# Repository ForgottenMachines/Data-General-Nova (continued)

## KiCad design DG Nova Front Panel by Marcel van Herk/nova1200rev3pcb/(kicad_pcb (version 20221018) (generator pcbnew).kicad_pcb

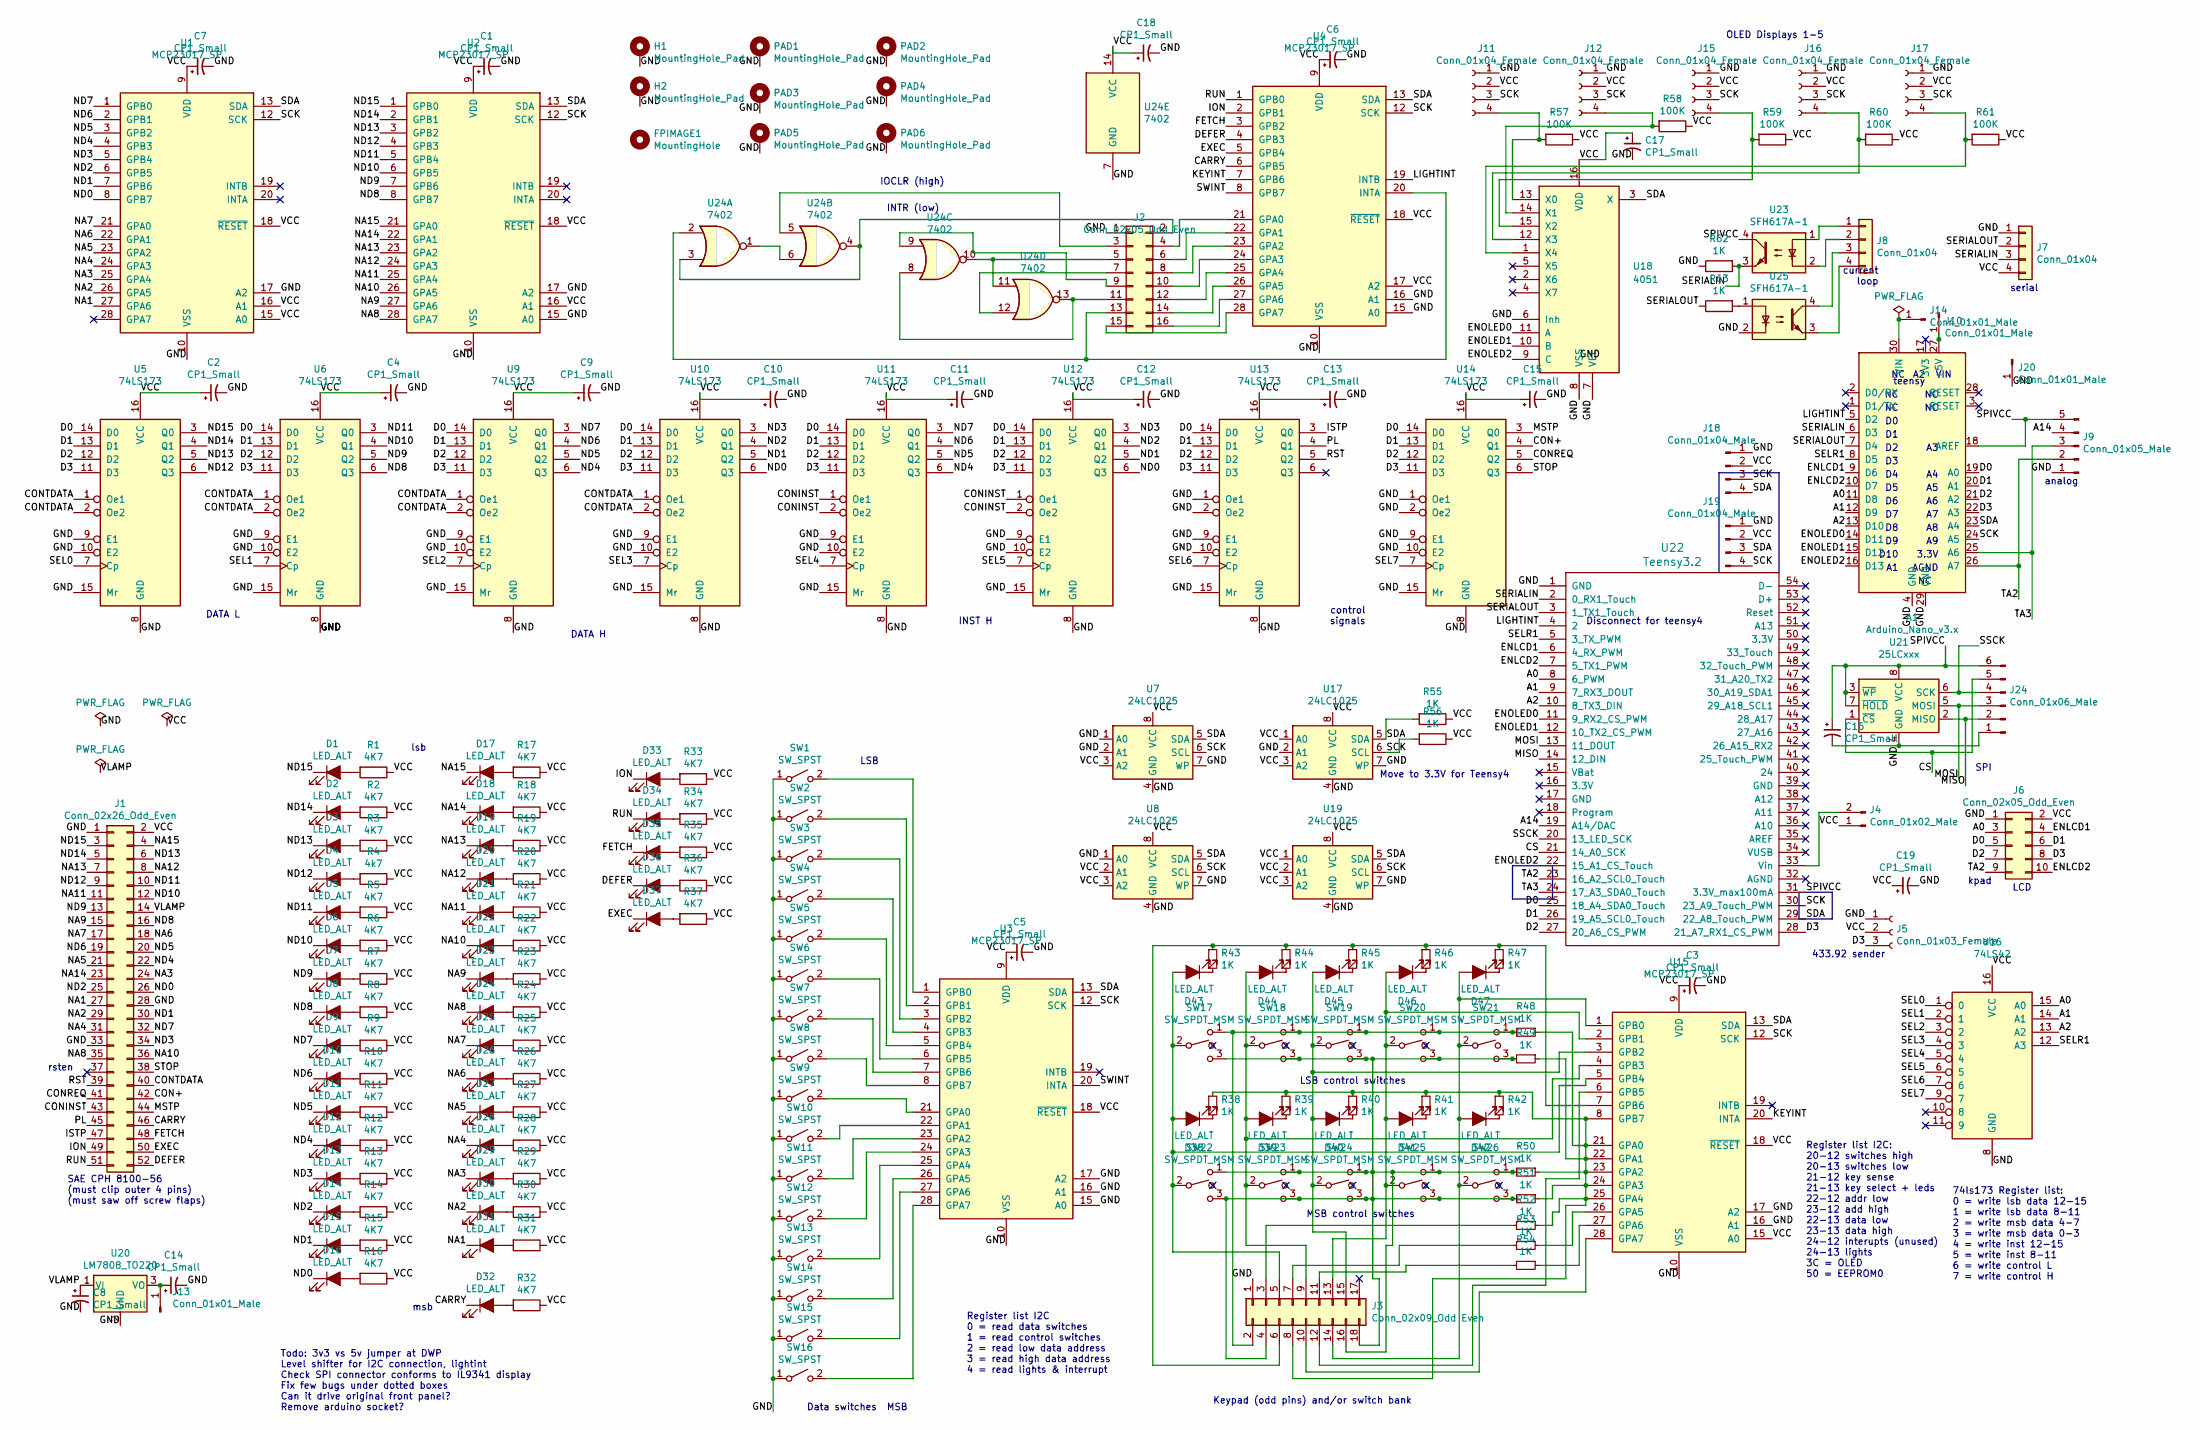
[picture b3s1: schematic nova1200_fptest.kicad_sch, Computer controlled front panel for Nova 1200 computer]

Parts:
A1: Arduino_Nano_v3.x; Arduino_Nano
C1, C2, C3, C4, C5, C6, C7, C8, C9, C10, C11, C12, C13, C14, C15, C16, C17, C18, C19: CP1_Small; CP_Radial_Tantal_D5.0mm_P5.00mm
D1, D2, D3, D4, D5, D6, D7, D8, D9, D10, D11, D12, D13, D14, D15, D16, D17, D18, D19, D20, D21, D22, D23, D24, D25, D26, D27, D28, D29, D30, D31, D32, D33, D34, D35, D36, D37, D38, D39, D40, D41, D42, D43, D44, D45, D46, D47: LED_ALT; LED_D5.0mm_Clear
FPIMAGE1: MountingHole; nova frontpanel layout
H1, H2: MountingHole_Pad; MountingHole_2.2mm_M2_Pad
J1: Conn_02x26_Odd_Even; nova_fp
J2: Conn_02x05_Odd_Even; PinHeader_2x08_P2.54mm_Vertical
J3: Conn_02x09_Odd Even; PinHeader_2x09_P2.54mm_Vertical
J4: Conn_01x02_Male; PinHeader_1x02_P2.54mm_Vertical
J5: Conn_01x03_Female; PinSocket_1x03_P2.54mm_Vertical
J6: Conn_02x05_Odd_Even; PinHeader_2x05_P2.54mm_Vertical
J7, J8: Conn_01x04; PinHeader_1x04_P2.54mm_Vertical
J9: Conn_01x05_Male; PinHeader_1x05_P2.54mm_Vertical
J10, J13, J14, J20: Conn_01x01_Male; PinHeader_1x01_P2.54mm_Vertical
J11, J12, J15, J16, J17: Conn_01x04_Female; PinSocket_1x04_P2.54mm_Vertical
J18, J19: Conn_01x04_Male; PinSocket_1x04_P2.54mm_Vertical
J24: Conn_01x06_Male; PinHeader_1x06_P2.54mm_Vertical
PAD1, PAD2, PAD3, PAD4, PAD5, PAD6: MountingHole_Pad; MountingHole_3.2mm_M3_Pad
R1, R2, R3, R5, R6, R7, R8, R9, R10, R11, R12, R13, R14, R15, R16, R17, R18, R19, R20, R21, R22, R23, R24, R25, R26, R27, R28, R29, R30, R31, R32, R33, R34, R35, R36, R37: 4K7; R_Axial_DIN0204_L3.6mm_D1.6mm_P7.62mm_Horizontal
R4: 4k7; R_Axial_DIN0204_L3.6mm_D1.6mm_P7.62mm_Horizontal
R38, R39, R40, R41, R42, R43, R44, R45, R46, R47, R48, R49, R50, R51, R52, R53, R54, R55, R56, R62, R63: 1K; R_Axial_DIN0204_L3.6mm_D1.6mm_P7.62mm_Horizontal
R57, R58, R59, R60, R61: 100K; R_Axial_DIN0204_L3.6mm_D1.6mm_P7.62mm_Horizontal
SW1, SW2, SW3, SW4, SW5, SW6, SW7, SW8, SW9, SW10, SW11, SW12, SW13, SW14, SW15, SW16: SW_SPST; multicomp switch
SW17, SW18, SW19, SW20, SW21, SW22, SW23, SW24, SW25, SW26: SW_SPDT_MSM; multicomp switch
U1, U2, U3, U4, U15: MCP23017_SP; DIP-28_W7.62mm
U5, U6, U9, U10, U11, U12, U13, U14: 74LS173; DIP-16_W7.62mm
U7, U8, U17, U19: 24LC1025; DIP-8_W7.62mm
U16: 74LS42; DIP-16_W7.62mm
U18: 4051; DIP-16_W7.62mm
U20: LM7808_TO220; TO-220-3_Horizontal_TabDown
U21: 25LCxxx; DIP-8_W7.62mm
U22: Teensy3.2; Teensy30_31_32_LC
U23, U25: SFH617A-1; DIP-4_W7.62mm
U24: 7402; DIP-14_W7.62mm

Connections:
/A0: A1.11 (D8), J6.3, U16.15 (A0), U22.8 (6_PWM)
/A1: A1.12 (D9), U16.14 (A1), U22.9 (7_RX3_DOUT)
/A2: A1.13 (D10), U16.13 (A2), U22.10 (8_TX3_DIN)
/A14: J9.4, U22.19 (A14/DAC)
/CARRY: D32.1 (K), J1.46, U4.6 (GPB5)
/CON+: J1.42, U14.4 (Q1)
/CONINST: J1.43, U11.1 (Oe1), U11.2 (Oe2), U12.1 (Oe1), U12.2 (Oe2)
/CONREQ: J1.41, U14.5 (Q2)
/CONTDATA: J1.40, U5.1 (Oe1), U5.2 (Oe2), U6.1 (Oe1), U6.2 (Oe2), U9.1 (Oe1), U9.2 (Oe2), U10.1 (Oe1), U10.2 (Oe2)
/CS: J24.5, U21.1 (~CS), U22.21 (14_A0_SCK)
/D0: A1.19 (A0), J6.5, U5.14 (D0), U6.14 (D0), U9.14 (D0), U10.14 (D0), U11.14 (D0), U12.14 (D0), U13.14 (D0), U14.14 (D0), U22.25 (18_A4_SDA0_Touch)
/D1: A1.20 (A1), J6.6, U5.13 (D1), U6.13 (D1), U9.13 (D1), U10.13 (D1), U11.13 (D1), U12.13 (D1), U13.13 (D1), U14.13 (D1), U22.26 (19_A5_SCL0_Touch)
/D2: A1.21 (A2), J6.7, U5.12 (D2), U6.12 (D2), U9.12 (D2), U10.12 (D2), U11.12 (D2), U12.12 (D2), U13.12 (D2), U14.12 (D2), U22.27 (20_A6_CS_PWM)
/D3: A1.22 (A3), J5.3, J6.8, U5.11 (D3), U6.11 (D3), U9.11 (D3), U10.11 (D3), U11.11 (D3), U12.11 (D3), U13.11 (D3), U14.11 (D3), U22.28 (21_A7_RX1_CS_PWM)
/DEFER: D36.1 (K), J1.52, U4.4 (GPB3)
/ENLCD1: A1.9 (D6), J6.4, U22.6 (4_RX_PWM)
/ENLCD2: A1.10 (D7), J6.10, U22.7 (5_TX1_PWM)
/ENOLED0: A1.14 (D11), U18.11 (A), U22.11 (9_RX2_CS_PWM)
/ENOLED1: A1.15 (D12), U18.10 (B), U22.12 (10_TX2_CS_PWM)
/ENOLED2: A1.16 (D13), U18.9 (C), U22.22 (15_A1_CS_Touch)
/EXEC: D37.1 (K), J1.50, U4.5 (GPB4)
/FETCH: D35.1 (K), J1.48, U4.3 (GPB2)
/GND: A1.4 (GND), A1.29 (GND), C1.2, C2.2, C3.2, C4.2, C5.2, C6.2, C7.2, C8.2, C9.2, C10.2, C11.2, C12.2, C13.2, C14.2, C15.2, C16.2, C17.2, C18.2, C19.2, H1.1, H2.1, J1.1, J1.28, J1.33, J2.1, J3.1, J5.1, J6.1, J7.1, J9.1, J11.1, J12.1, J15.1, J16.1, J17.1, J18.1, J19.1, J20.1, J24.1, PAD1.1, PAD2.1, PAD3.1, PAD4.1, PAD5.1, PAD6.1, R62.1, SW1.1 (A), SW2.1 (A), SW3.1 (A), SW4.1 (A), SW5.1 (A), SW6.1 (A), SW7.1 (A), SW8.1 (A), SW9.1 (A), SW10.1 (A), SW11.1 (A), SW12.1 (A), SW13.1 (A), SW14.1 (A), SW15.1 (A), SW16.1 (A), U1.10 (VSS), U1.17 (A2), U2.10 (VSS), U2.15 (A0), U2.17 (A2), U3.10 (VSS), U3.15 (A0), U3.16 (A1), U3.17 (A2), U4.10 (VSS), U4.15 (A0), U4.16 (A1), U5.8 (GND), U5.9 (E1), U5.10 (E2), U5.15 (Mr), U6.8 (GND), U6.9 (E1), U6.10 (E2), U6.15 (Mr), U7.1 (A0), U7.2 (A1), U7.4 (GND), U7.7 (WP), U8.1 (A0), U8.4 (GND), U8.7 (WP), U9.8 (GND), U9.9 (E1), U9.10 (E2), U9.15 (Mr), U10.8 (GND), U10.9 (E1), U10.10 (E2), U10.15 (Mr), U11.8 (GND), U11.9 (E1), U11.10 (E2), U11.15 (Mr), U12.8 (GND), U12.9 (E1), U12.10 (E2), U12.15 (Mr), U13.1 (Oe1), U13.2 (Oe2), U13.8 (GND), U13.9 (E1), U13.10 (E2), U13.15 (Mr), U14.1 (Oe1), U14.2 (Oe2), U14.8 (GND), U14.9 (E1), U14.10 (E2), U14.15 (Mr), U15.10 (VSS), U15.16 (A1), U15.17 (A2), U16.8 (GND), U17.2 (A1), U17.4 (GND), U17.7 (WP), U18.6 (Inh), U18.7 (VEE), U18.8 (VSS), U19.4 (GND), U19.7 (WP), U20.2 (GND), U21.4 (GND), U22.1 (GND), U24.7 (GND), U25.2
/ION: D33.1 (K), J1.49, U4.2 (GPB1)
/ISTP: J1.47, U13.3 (Q0)
/KEYINT: U4.7 (GPB6), U15.20 (INTA)
/LIGHTINT: A1.5 (D2), U4.19 (INTB), U22.4 (2)
/MISO: J24.2, U21.2 (MISO), U22.14 (12_DIN)
/MOSI: J24.3, U21.5 (MOSI), U22.13 (11_DOUT)
/MSTP: J1.44, U14.3 (Q0)
/NA1: D31.1 (K), J1.27, U1.27 (GPA6)
/NA2: D30.1 (K), J1.29, U1.26 (GPA5)
/NA3: D29.1 (K), J1.24, U1.25 (GPA4)
/NA4: D28.1 (K), J1.31, U1.24 (GPA3)
/NA5: D27.1 (K), J1.21, U1.23 (GPA2)
/NA6: D26.1 (K), J1.18, U1.22 (GPA1)
/NA7: D25.1 (K), J1.17, U1.21 (GPA0)
/NA8: D24.1 (K), J1.35, U2.28 (GPA7)
/NA9: D23.1 (K), J1.15, U2.27 (GPA6)
/NA10: D22.1 (K), J1.36, U2.26 (GPA5)
/NA11: D21.1 (K), J1.11, U2.25 (GPA4)
/NA12: D20.1 (K), J1.8, U2.24 (GPA3)
/NA13: D19.1 (K), J1.7, U2.23 (GPA2)
/NA14: D18.1 (K), J1.23, U2.22 (GPA1)
/NA15: D17.1 (K), J1.4, U2.21 (GPA0)
/ND0: D16.1 (K), J1.26, U1.8 (GPB7), U10.6 (Q3), U12.6 (Q3)
/ND1: D15.1 (K), J1.30, U1.7 (GPB6), U10.5 (Q2), U12.5 (Q2)
/ND2: D14.1 (K), J1.25, U1.6 (GPB5), U10.4 (Q1), U12.4 (Q1)
/ND3: D13.1 (K), J1.34, U1.5 (GPB4), U10.3 (Q0), U12.3 (Q0)
/ND4: D12.1 (K), J1.22, U1.4 (GPB3), U9.6 (Q3), U11.6 (Q3)
/ND5: D11.1 (K), J1.20, U1.3 (GPB2), U9.5 (Q2), U11.5 (Q2)
/ND6: D10.1 (K), J1.19, U1.2 (GPB1), U9.4 (Q1), U11.4 (Q1)
/ND7: D9.1 (K), J1.32, U1.1 (GPB0), U9.3 (Q0), U11.3 (Q0)
/ND8: D8.1 (K), J1.16, U2.8 (GPB7), U6.6 (Q3)
/ND9: D7.1 (K), J1.13, U2.7 (GPB6), U6.5 (Q2)
/ND10: D6.1 (K), J1.12, U2.6 (GPB5), U6.4 (Q1)
/ND11: D5.1 (K), J1.10, U2.5 (GPB4), U6.3 (Q0)
/ND12: D4.1 (K), J1.9, U2.4 (GPB3), U5.6 (Q3)
/ND13: D3.1 (K), J1.6, U2.3 (GPB2), U5.5 (Q2)
/ND14: D2.1 (K), J1.5, U2.2 (GPB1), U5.4 (Q1)
/ND15: D1.1 (K), J1.3, U2.1 (GPB0), U5.3 (Q0)
/PL: J1.45, U13.4 (Q1)
/RST: J1.39, U13.5 (Q2)
/RUN: D34.1 (K), J1.51, U4.1 (GPB0)
/SCK: A1.24 (A5), J11.3, J12.3, J15.3, J16.3, J17.3, J18.3, J19.4, R56.2, U1.12 (SCK), U2.12 (SCK), U3.12 (SCK), U4.12 (SCK), U7.6 (SCL), U8.6 (SCL), U15.12 (SCK), U17.6 (SCL), U19.6 (SCL), U22.30 (23_A9_Touch_PWM)
/SDA: A1.23 (A4), J18.4, J19.3, R55.2, U1.13 (SDA), U2.13 (SDA), U3.13 (SDA), U4.13 (SDA), U7.5 (SDA), U8.5 (SDA), U15.13 (SDA), U17.5 (SDA), U18.3 (X), U19.5 (SDA), U22.29 (22_A8_Touch_PWM)
/SEL0: U5.7 (Cp), U16.1 (0)
/SEL1: U6.7 (Cp), U16.2 (1)
/SEL2: U9.7 (Cp), U16.3 (2)
/SEL3: U10.7 (Cp), U16.4 (3)
/SEL4: U11.7 (Cp), U16.5 (4)
/SEL5: U12.7 (Cp), U16.6 (5)
/SEL6: U13.7 (Cp), U16.7 (6)
/SEL7: U14.7 (Cp), U16.9 (7)
/SELR1: A1.8 (D5), U16.12 (A3), U22.5 (3_TX_PWM)
/SERIALIN: A1.6 (D3), J7.3, R62.2, U22.2 (0_RX1_Touch), U23.3
/SERIALOUT: A1.7 (D4), J7.2, R63.1, U22.3 (1_TX1_Touch)
/SPIVCC: A1.18 (AREF), C16.1, J9.5, J24.6, U21.3 (~WP), U21.7 (~HOLD), U21.8 (VCC), U22.31 (3.3V_max100mA), U23.4
/SSCK: J24.4, U21.6 (SCK), U22.20 (13_LED_SCK)
/STOP: J1.38, U14.6 (Q3)
/SWINT: U3.20 (INTA), U4.8 (GPB7)
/TA2: A1.26 (A7), J6.9, J9.2, U22.23 (16_A2_SCL0_Touch)
/TA3: A1.25 (A6), J9.3, U22.24 (17_A3_SDA0_Touch)
/VCC: C1.1, C2.1, C3.1, C4.1, C5.1, C6.1, C7.1, C9.1, C10.1, C11.1, C12.1, C13.1, C15.1, C17.1, C18.1, C19.1, J1.2, J4.1, J5.2, J6.2, J7.4, J11.2, J12.2, J15.2, J16.2, J17.2, J18.2, J19.2, R1.1, R2.1, R3.1, R4.1, R5.1, R6.1, R7.1, R8.1, R9.1, R10.1, R11.1, R12.1, R13.1, R14.1, R15.1, R16.1, R17.1, R18.1, R19.1, R20.1, R21.1, R22.1, R23.1, R24.1, R25.1, R26.1, R27.1, R28.1, R29.1, R30.1, R31.1, R32.1, R33.1, R34.1, R35.1, R36.1, R37.1, R55.1, R56.1, R57.1, R58.1, R59.1, R60.1, R61.1, U1.9 (VDD), U1.15 (A0), U1.16 (A1), U1.18 (~RESET), U2.9 (VDD), U2.16 (A1), U2.18 (~RESET), U3.9 (VDD), U3.18 (~RESET), U4.9 (VDD), U4.17 (A2), U4.18 (~RESET), U5.16 (VCC), U6.16 (VCC), U7.3 (A2), U7.8 (VCC), U8.2 (A1), U8.3 (A2), U8.8 (VCC), U9.16 (VCC), U10.16 (VCC), U11.16 (VCC), U12.16 (VCC), U13.16 (VCC), U14.16 (VCC), U15.9 (VDD), U15.15 (A0), U15.18 (~RESET), U16.16 (VCC), U17.1 (A0), U17.3 (A2), U17.8 (VCC), U18.16 (VDD), U19.1 (A0), U19.2 (A1), U19.3 (A2), U19.8 (VCC), U24.14 (VCC)
/VLAMP: C8.1, J1.14, U20.1 (VI)
unnamed: A1.27 (+5V), J10.1
unnamed: A1.30 (VIN), J14.1
unnamed: C14.1, J13.1, U20.3 (VO)
unnamed: D1.2 (A), R1.2
unnamed: D2.2 (A), R2.2
unnamed: D3.2 (A), R3.2
unnamed: D4.2 (A), R4.2
unnamed: D5.2 (A), R5.2
unnamed: D6.2 (A), R6.2
unnamed: D7.2 (A), R7.2
unnamed: D8.2 (A), R8.2
unnamed: D9.2 (A), R9.2
unnamed: D10.2 (A), R10.2
unnamed: D11.2 (A), R11.2
unnamed: D12.2 (A), R12.2
unnamed: D13.2 (A), R13.2
unnamed: D14.2 (A), R14.2
unnamed: D15.2 (A), R15.2
unnamed: D16.2 (A), R16.2
unnamed: D17.2 (A), R17.2
unnamed: D18.2 (A), R18.2
unnamed: D19.2 (A), R19.2
unnamed: D20.2 (A), R20.2
unnamed: D21.2 (A), R21.2
unnamed: D22.2 (A), R22.2
unnamed: D23.2 (A), R23.2
unnamed: D24.2 (A), R24.2
unnamed: D25.2 (A), R25.2
unnamed: D26.2 (A), R26.2
unnamed: D27.2 (A), R27.2
unnamed: D28.2 (A), R28.2
unnamed: D29.2 (A), R29.2
unnamed: D30.2 (A), R30.2
unnamed: D31.2 (A), R31.2
unnamed: D32.2 (A), R32.2
unnamed: D33.2 (A), R33.2
unnamed: D34.2 (A), R34.2
unnamed: D35.2 (A), R35.2
unnamed: D36.2 (A), R36.2
unnamed: D37.2 (A), R37.2
unnamed: D38.1 (K), R38.2
unnamed: D38.2 (A), D43.2 (A), J3.5, SW17.2, SW22.2, U15.5 (GPB4)
unnamed: D39.1 (K), R39.2
unnamed: D39.2 (A), D44.2 (A), J3.9, SW18.2, SW23.2, U15.4 (GPB3)
unnamed: D40.1 (K), R40.2
unnamed: D40.2 (A), D45.2 (A), J3.15, SW19.2, SW24.2, U15.3 (GPB2)
unnamed: D41.1 (K), R41.2
unnamed: D41.2 (A), D46.2 (A), J3.13, SW20.2, SW25.2, U15.2 (GPB1)
unnamed: D42.1 (K), R42.2
unnamed: D42.2 (A), D47.2 (A), J3.14, SW21.2, SW26.2, U15.1 (GPB0)
unnamed: D43.1 (K), R43.2
unnamed: D44.1 (K), R44.2
unnamed: D45.1 (K), R45.2
unnamed: D46.1 (K), R46.2
unnamed: D47.1 (K), R47.2
unnamed: J2.2, U24.3, U24.4
unnamed: J2.3, U24.5
unnamed: J2.4, U4.21 (GPA0)
unnamed: J2.5, U24.10, U24.11
unnamed: J2.6, U4.22 (GPA1)
unnamed: J2.7, U24.12
unnamed: J2.8, U4.23 (GPA2)
unnamed: J2.9, U24.9
unnamed: J2.10, U4.24 (GPA3)
unnamed: J2.11, U24.8, U24.13
unnamed: J2.12, U4.25 (GPA4)
unnamed: J2.13, U4.20 (INTA), U24.2
unnamed: J2.14, U4.26 (GPA5)
unnamed: J2.15, U4.28 (GPA7)
unnamed: J2.16, U4.27 (GPA6)
unnamed: J3.2, R48.2, SW17.1, SW18.1, SW19.1, SW20.1, SW21.1
unnamed: J3.3, R52.2
unnamed: J3.6, R43.1, R44.1, R45.1, R46.1, R47.1, U15.7 (GPB6)
unnamed: J3.7, R53.2
unnamed: J3.10, U15.28 (GPA7)
unnamed: J3.11, R54.2
unnamed: J3.12, U15.6 (GPB5)
unnamed: J4.2, U22.33 (Vin)
unnamed: J8.1, U23.1
unnamed: J8.2, U23.2
unnamed: J8.3, U25.4
unnamed: J8.4, U25.3
unnamed: J11.4, R57.2, U18.13 (X0)
unnamed: J12.4, R58.2, U18.14 (X1)
unnamed: J15.4, R59.2, U18.15 (X2)
unnamed: J16.4, R60.2, U18.12 (X3)
unnamed: J17.4, R61.2, U18.1 (X4)
unnamed: R53.1, U15.26 (GPA5)
unnamed: R54.1, U15.27 (GPA6)
unnamed: R63.2, U25.1
unnamed: SW1.2 (B), U3.1 (GPB0)
unnamed: SW2.2 (B), U3.2 (GPB1)
unnamed: SW3.2 (B), U3.3 (GPB2)
unnamed: SW4.2 (B), U3.4 (GPB3)
unnamed: SW5.2 (B), U3.5 (GPB4)
unnamed: SW6.2 (B), U3.6 (GPB5)
unnamed: SW7.2 (B), U3.7 (GPB6)
unnamed: SW8.2 (B), U3.8 (GPB7)
unnamed: SW9.2 (B), U3.21 (GPA0)
unnamed: SW10.2 (B), U3.22 (GPA1)
unnamed: SW11.2 (B), U3.23 (GPA2)
unnamed: SW12.2 (B), U3.24 (GPA3)
unnamed: SW13.2 (B), U3.25 (GPA4)
unnamed: SW14.2 (B), U3.26 (GPA5)
unnamed: SW15.2 (B), U3.27 (GPA6)
unnamed: SW16.2 (B), U3.28 (GPA7)
unnamed: U24.1, U24.6

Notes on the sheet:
433.92 sender
Keypad (odd pins) and/or switch bank
74ls173 Register list: 0 = write lsb data 12-15 1 = write lsb data 8-11 2 = write msb data 4-7 3 = write msb data 0-3 4 = write inst 12-15 5 = write inst 8-11 6 = write control L 7 = write control H
rsten
SAE CPH 8100-56 (must clip outer 4 pins) (must saw off screw flaps)
D10
teensy
AGND
Data switches
Move to 3.3V for Teensy4
MSB
INST H
LCD
VIN
LSB control switches
control signals
INTR (low)
OLED Displays 1-5
DATA H
lsb
Register list I2C 0 = read data switches 1 = read control switches 2 = read low data address 3 = read high data address 4 = read lights & interrupt
3.3V
Todo: 3v3 vs 5v jumper at DWP Level shifter for I2C connection, lightint Check SPI connector conforms to IL9341 display Fix few bugs under dotted boxes Can it drive original front panel? Remove arduino socket?
analog
DATA L
msb
kpad
SPI
Register list I2C: 20-12 switches high 20-13 switches low 21-12 key sense 21-13 key select + leds 22-12 addr low 23-12 add high 22-13 data low 23-13 data high 24-12 interupts (unused) 24-13 lights 3C = OLED 50 = EEPROM0
serial
Disconnect for teensy4
MSB control switches
LSB
current loop
IOCLR (high)

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
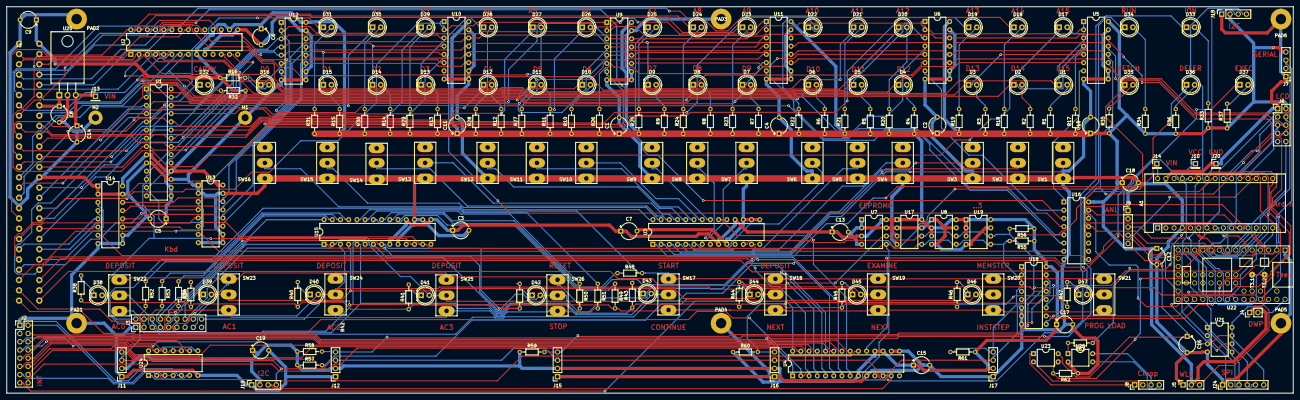
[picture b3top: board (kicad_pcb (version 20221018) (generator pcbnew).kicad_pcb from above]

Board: 2 copper layers, 397.5 x 119.4 mm, 211 parts (0 on the bottom side), 201 nets.

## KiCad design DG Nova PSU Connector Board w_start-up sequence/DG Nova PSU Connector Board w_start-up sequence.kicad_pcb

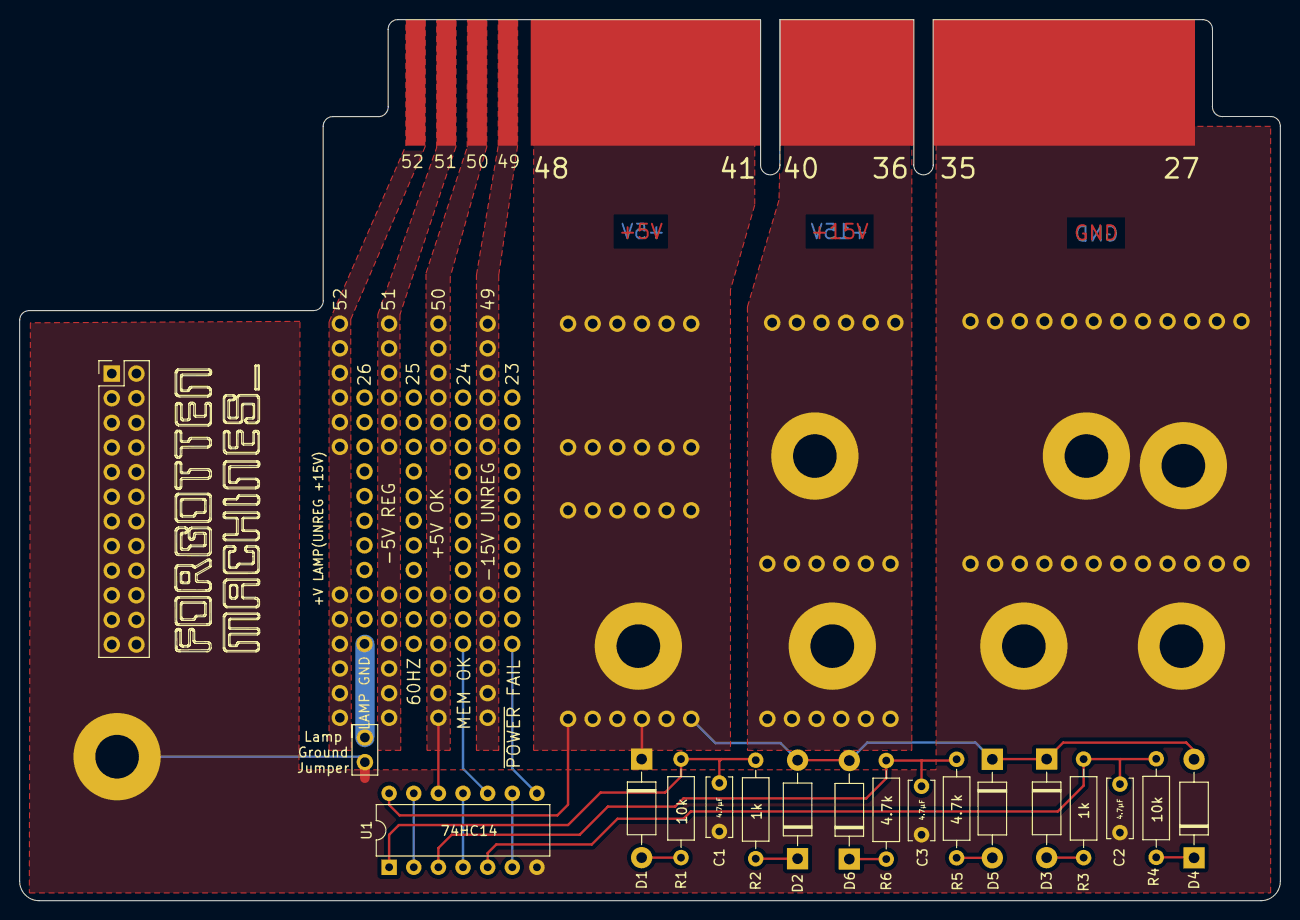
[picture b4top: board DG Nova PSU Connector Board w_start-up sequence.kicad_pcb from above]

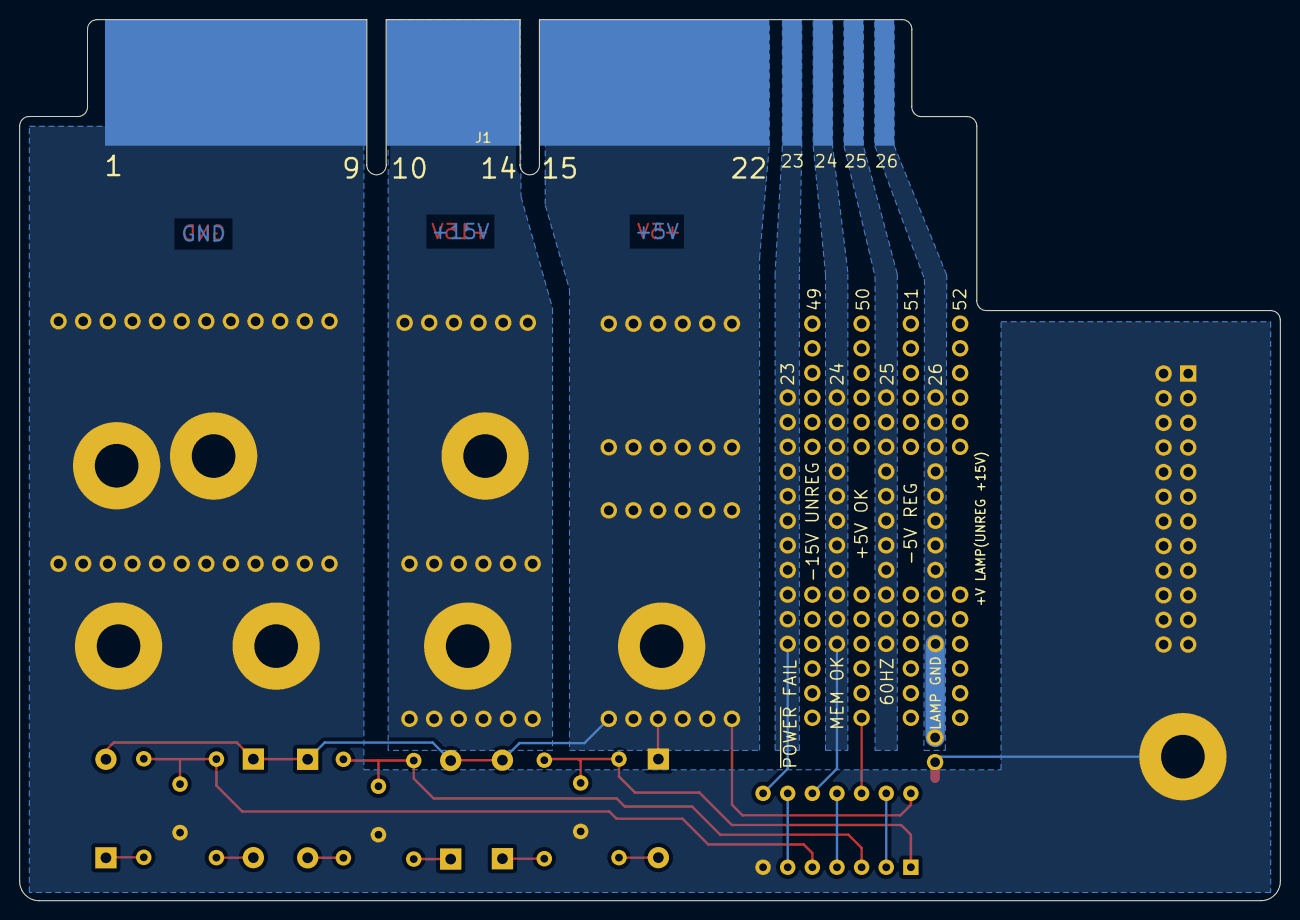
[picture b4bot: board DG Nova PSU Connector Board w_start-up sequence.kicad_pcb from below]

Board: 2 copper layers, 130.0 x 90.8 mm, 48 parts (5 on the bottom side), 24 nets.

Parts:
 : Conn_01x02; PinHeader_1x02_P2.54mm_Vertical
.: PinHeader_2x12_P2.54mm_Vertical
C1, C2, C3: C; C_Disc_D6.0mm_W2.5mm_P5.00mm
D1, D2, D3, D4, D5, D6: 1N4004; D_DO-41_SOD81_P10.16mm_Horizontal
H1, H2, H4, H5, H6, H7, H8, H9: MountingHole_Pad; MountingHole_4.5mm_Pad
J1: Conn_02x07_Counter_Clockwise; 52 Pin Connector
J2, J3: Conn_01x12; PinHeader_1x12_P2.54mm_Vertical
J8, J9, J10, J11, J12, J13, J14, J15, J16, J17, J18, J19, J20, J21, J22: Conn_01x06; PinHeader_1x06_P2.54mm
J23, J24, J25, J26: Conn_01x11; PinHeader_1x11_P2.54mm
R1, R2, R3, R4, R5, R6: 10K; R_Axial_DIN0207_L6.3mm_D2.5mm_P10.16mm_Horizontal
U1: 74HC14; DIP-14_W7.62mm

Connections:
14: J21.1, J21.2, J21.3, J21.4, J21.5, J21.6, J22.1, J22.2, J22.3, J22.4, J22.5, J22.6
23 PWR FAIL: J1.4, J23.1, J23.2, J23.3, J23.4, J23.5, J23.6, J23.7, J23.8, J23.9, J23.10, J23.11, U1.8
24 MEM OK: J1.5, J24.1, J24.2, J24.3, J24.4, J24.5, J24.6, J24.7, J24.8, J24.9, J24.10, J24.11, U1.10
25: J1.6, J25.1, J25.2, J25.3, J25.4, J25.5, J25.6, J25.7, J25.8, J25.9, J25.10, J25.11
26: J1.7, J26.1, J26.2, J26.3, J26.4, J26.5, J26.6, J26.7, J26.8, J26.9
49: J1.11, J15.1, J15.2, J15.3, J15.4, J15.5, J15.6, J16.1, J16.2, J16.3, J16.4, J16.5, J16.6
50 +5v OK: J1.12, J17.1, J17.2, J17.3, J17.4, J17.5, J17.6, J18.1, J18.2, J18.3, J18.4, J18.5, J18.6, U1.12
51: J1.13, J19.1, J19.2, J19.3, J19.4, J19.5, J19.6, J20.1, J20.2, J20.3, J20.4, J20.5, J20.6
+5V: D1.1 (K), D2.2 (A), D3.1 (K), D4.2 (A), D5.1 (K), D6.2 (A), H6.1, J1.3, J1.10, J11.1, J11.2, J11.3, J11.4, J11.5, J11.6, J12.1, J12.2, J12.3, J12.4, J12.5, J12.6, J13.1, J13.2, J13.3, J13.4, J13.5, J13.6, J14.1, J14.2, J14.3, J14.4, J14.5, J14.6, U1.14 (VCC)
+15V: H5.1, H8.1, J1.2, J1.9, J8.1, J8.2, J8.3, J8.4, J8.5, J8.6, J9.1, J9.2, J9.3, J9.4, J9.5, J9.6, J10.1, J10.2, J10.3, J10.4, J10.5, J10.6
GND: .2, ..1, ..2, ..3, ..4, ..5, ..6, ..7, ..8, ..9, ..10, ..11, ..12, ..13, ..14, ..15, ..16, ..17, ..18, ..19, ..20, ..21, ..22, ..23, ..24, C1.2, C2.2, C3.2, H1.1, H2.1, H4.1, H7.1, H9.1, J1.1, J1.8, J2.1, J2.2, J2.3, J2.4, J2.5, J2.6, J2.7, J2.8, J2.9, J2.10, J2.11, J2.12, J3.1, J3.2, J3.3, J3.4, J3.5, J3.6, J3.7, J3.8, J3.9, J3.10, J3.11, J3.12, U1.7 (GND)
LampGND: .1, J26.10, J26.11
unnamed: C1.1, R1.2, R2.1, U1.1
unnamed: C2.1, R3.2, R4.1, U1.5
unnamed: C3.1, R5.2, R6.1, U1.3
unnamed: D1.2 (A), R1.1
unnamed: D2.1 (K), R2.2
unnamed: D3.2 (A), R3.1
unnamed: D4.1 (K), R4.2
unnamed: D5.2 (A), R5.1
unnamed: D6.1 (K), R6.2
unnamed: U1.6, U1.9
unnamed: U1.4, U1.11
unnamed: U1.2, U1.13

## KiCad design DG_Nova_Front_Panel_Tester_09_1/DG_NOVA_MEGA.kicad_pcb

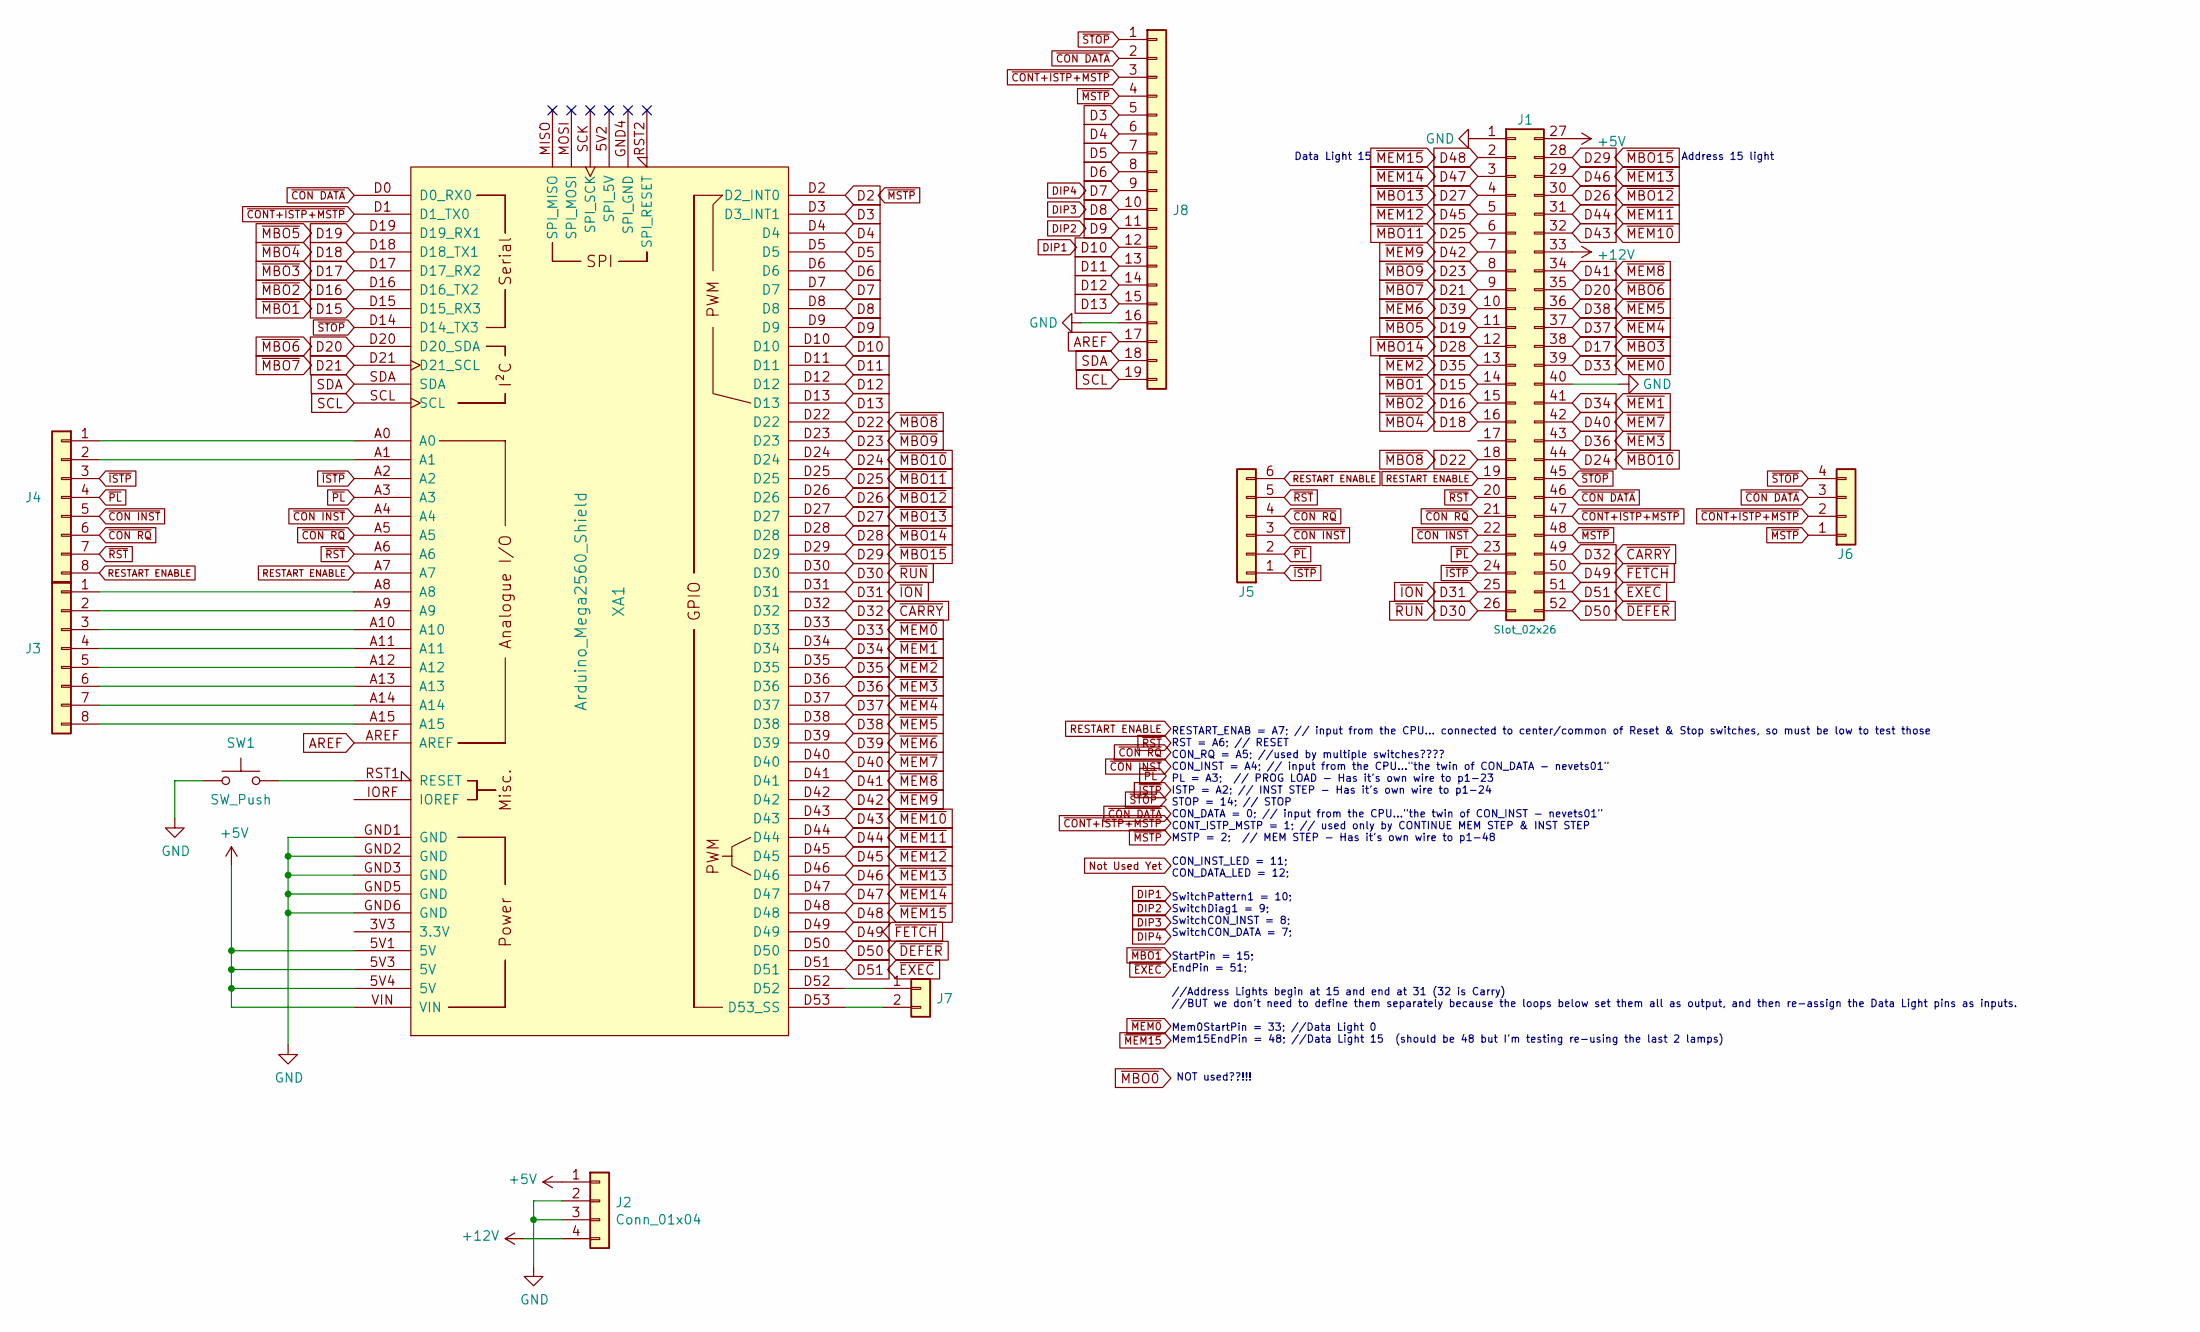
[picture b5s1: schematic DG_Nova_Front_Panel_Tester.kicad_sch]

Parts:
J1: Slot_02x26; port_Nova_52pin
J2, J6: Conn_01x04; PinHeader_1x04_P2.54mm_Vertical
J3, J4: Conn_01x08; PinHeader_1x08_P2.54mm_Vertical
J5: Conn_01x06; PinHeader_1x06_P2.54mm_Vertical
J7: Conn_01x02; PinHeader_1x02_P2.54mm_Vertical
J8: Conn_01x19; PinHeader_1x19_P2.54mm_Vertical
SW1: SW_Push; SW_PUSH_6mm
XA1: Arduino_Mega2560_Shield

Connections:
52: J7.2, XA1.D53 (D53_SS)
53: J7.1, XA1.D52
+5V: J1.27, J2.1, XA1.5V1 (5V), XA1.5V3 (5V), XA1.5V4 (5V), XA1.VIN
+12V: J1.33, J2.4
A0: J4.1, XA1.A0
A1: J4.2, XA1.A1
A2: J1.24, J4.3, J5.1, XA1.A2
A3: J1.23, J4.4, J5.2, XA1.A3
A4: J1.22, J4.5, J5.3, XA1.A4
A5: J1.21, J4.6, J5.4, XA1.A5
A6: J1.20, J4.7, J5.5, XA1.A6
A7: J1.19, J4.8, J5.6, XA1.A7
A8: J3.1, XA1.A8
A9: J3.2, XA1.A9
A10: J3.3, XA1.A10
A11: J3.4, XA1.A11
A12: J3.5, XA1.A12
A13: J3.6, XA1.A13
A14: J3.7, XA1.A14
A15: J3.8, XA1.A15
AREF: J8.17, XA1.AREF
D0: J1.46, J6.3, J8.2, XA1.D0 (D0_RX0)
D1: J1.47, J6.2, J8.3, XA1.D1 (D1_TX0)
D3: J8.5, XA1.D3 (D3_INT1)
D4: J8.6, XA1.D4
D5: J8.7, XA1.D5
D6: J8.8, XA1.D6
D7: J8.9, XA1.D7
D8: J8.10, XA1.D8
D9: J8.11, XA1.D9
D10: J8.12, XA1.D10
D11: J8.13, XA1.D11
D12: J8.14, XA1.D12
D13: J8.15, XA1.D13
D14: J1.45, J6.4, J8.1, XA1.D14 (D14_TX3)
D15: J1.14, XA1.D15 (D15_RX3)
D16: J1.15, XA1.D16 (D16_TX2)
D17: J1.38, XA1.D17 (D17_RX2)
D18: J1.16, XA1.D18 (D18_TX1)
D19: J1.11, XA1.D19 (D19_RX1)
D20: J1.35, XA1.D20 (D20_SDA)
D21: J1.9, XA1.D21 (D21_SCL)
D22: J1.18, XA1.D22
D23: J1.8, XA1.D23
D24: J1.44, XA1.D24
D25: J1.6, XA1.D25
D26: J1.30, XA1.D26
D27: J1.4, XA1.D27
D28: J1.12, XA1.D28
D29: J1.28, XA1.D29
D30: J1.26, XA1.D30
D31: J1.25, XA1.D31
D32: J1.49, XA1.D32
D33: J1.39, XA1.D33
D34: J1.41, XA1.D34
D35: J1.13, XA1.D35
D36: J1.43, XA1.D36
D37: J1.37, XA1.D37
D38: J1.36, XA1.D38
D39: J1.10, XA1.D39
D40: J1.42, XA1.D40
D41: J1.34, XA1.D41
D42: J1.7, XA1.D42
D43: J1.32, XA1.D43
D44: J1.31, XA1.D44
D45: J1.5, XA1.D45
D46: J1.29, XA1.D46
D47: J1.3, XA1.D47
D48: J1.2, XA1.D48
D49: J1.50, XA1.D49
D50: J1.52, XA1.D50
D51: J1.51, XA1.D51
GND: J1.1, J1.40, J2.2, J2.3, J8.16, SW1.1, XA1.GND1 (GND), XA1.GND2 (GND), XA1.GND3 (GND), XA1.GND5 (GND), XA1.GND6 (GND); also elsewhere on the board
unnamed 74: SW1.2, XA1.RST1 (RESET); also elsewhere on the board
SCL: J8.19, XA1.SCL
SDA: J8.18, XA1.SDA

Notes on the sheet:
Address 15 light
RESTART_ENAB = A7; // input from the CPU... connected to center/common of Reset & Stop switches, so must be low to test those RST = A6; // RESET CON_RQ = A5; //used by multiple switches???? CON_INST = A4; // input from the CPU..."the twin of CON_DATA - nevets01" PL = A3; // PROG LOAD - Has it's own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
Data Light 15
NOT used??!!!

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
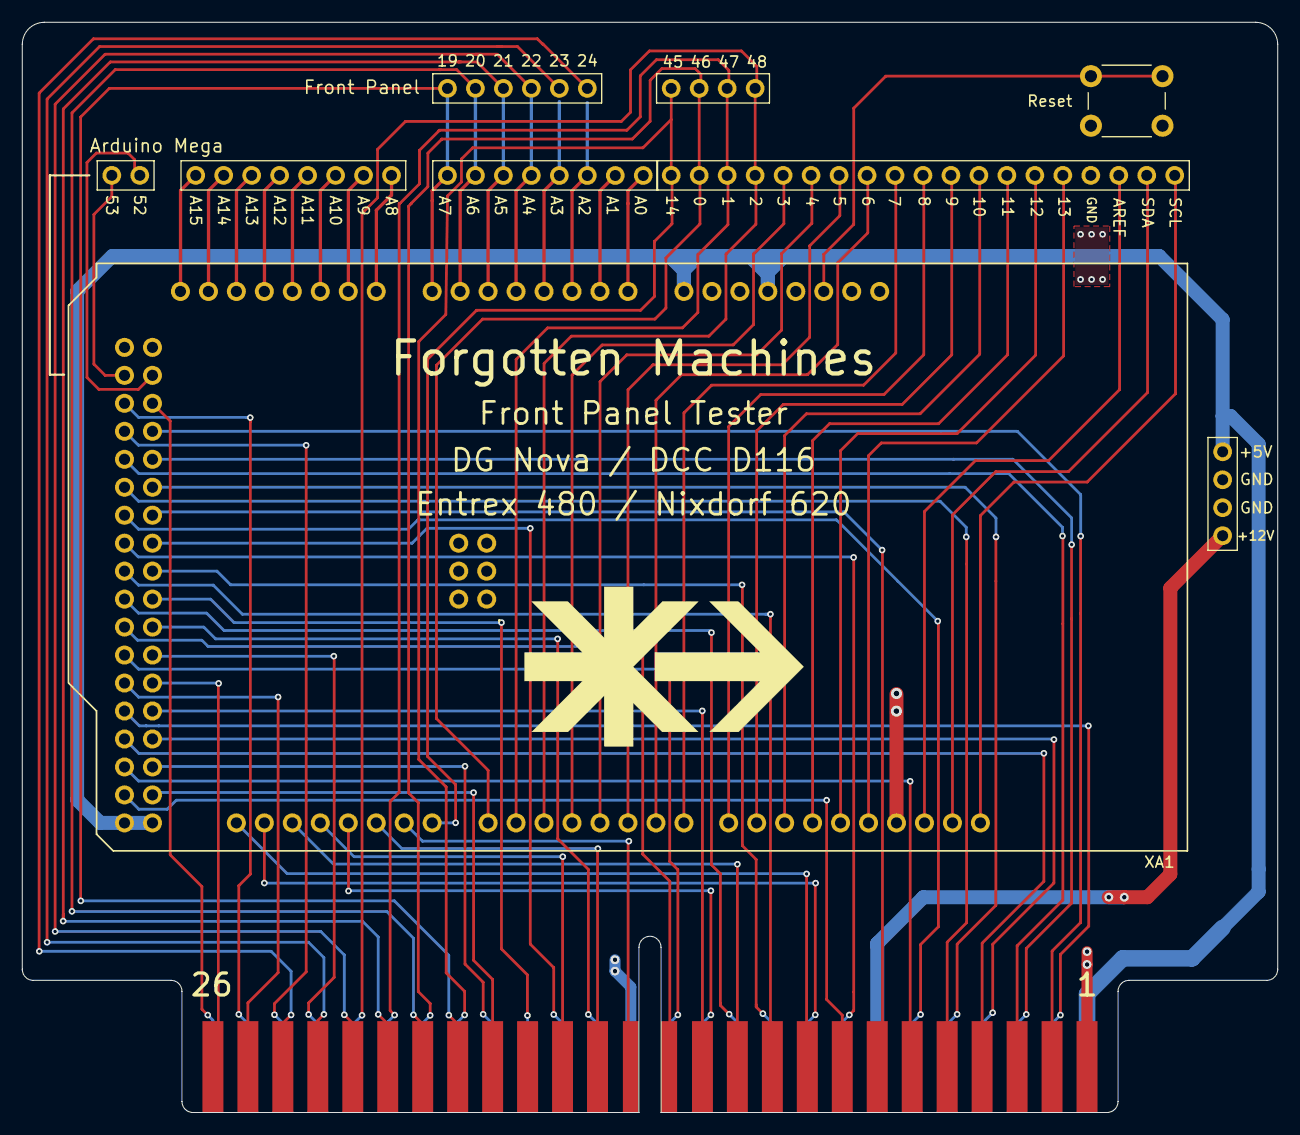
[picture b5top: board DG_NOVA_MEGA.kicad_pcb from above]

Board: 2 copper layers, 114.0 x 99.0 mm, 10 parts (0 on the bottom side), 77 nets.

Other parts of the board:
Reset: SW_Push; SW_PUSH_6mm

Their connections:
GND: Reset.1; also elsewhere on the board
unnamed 74: Reset.2; also elsewhere on the board
